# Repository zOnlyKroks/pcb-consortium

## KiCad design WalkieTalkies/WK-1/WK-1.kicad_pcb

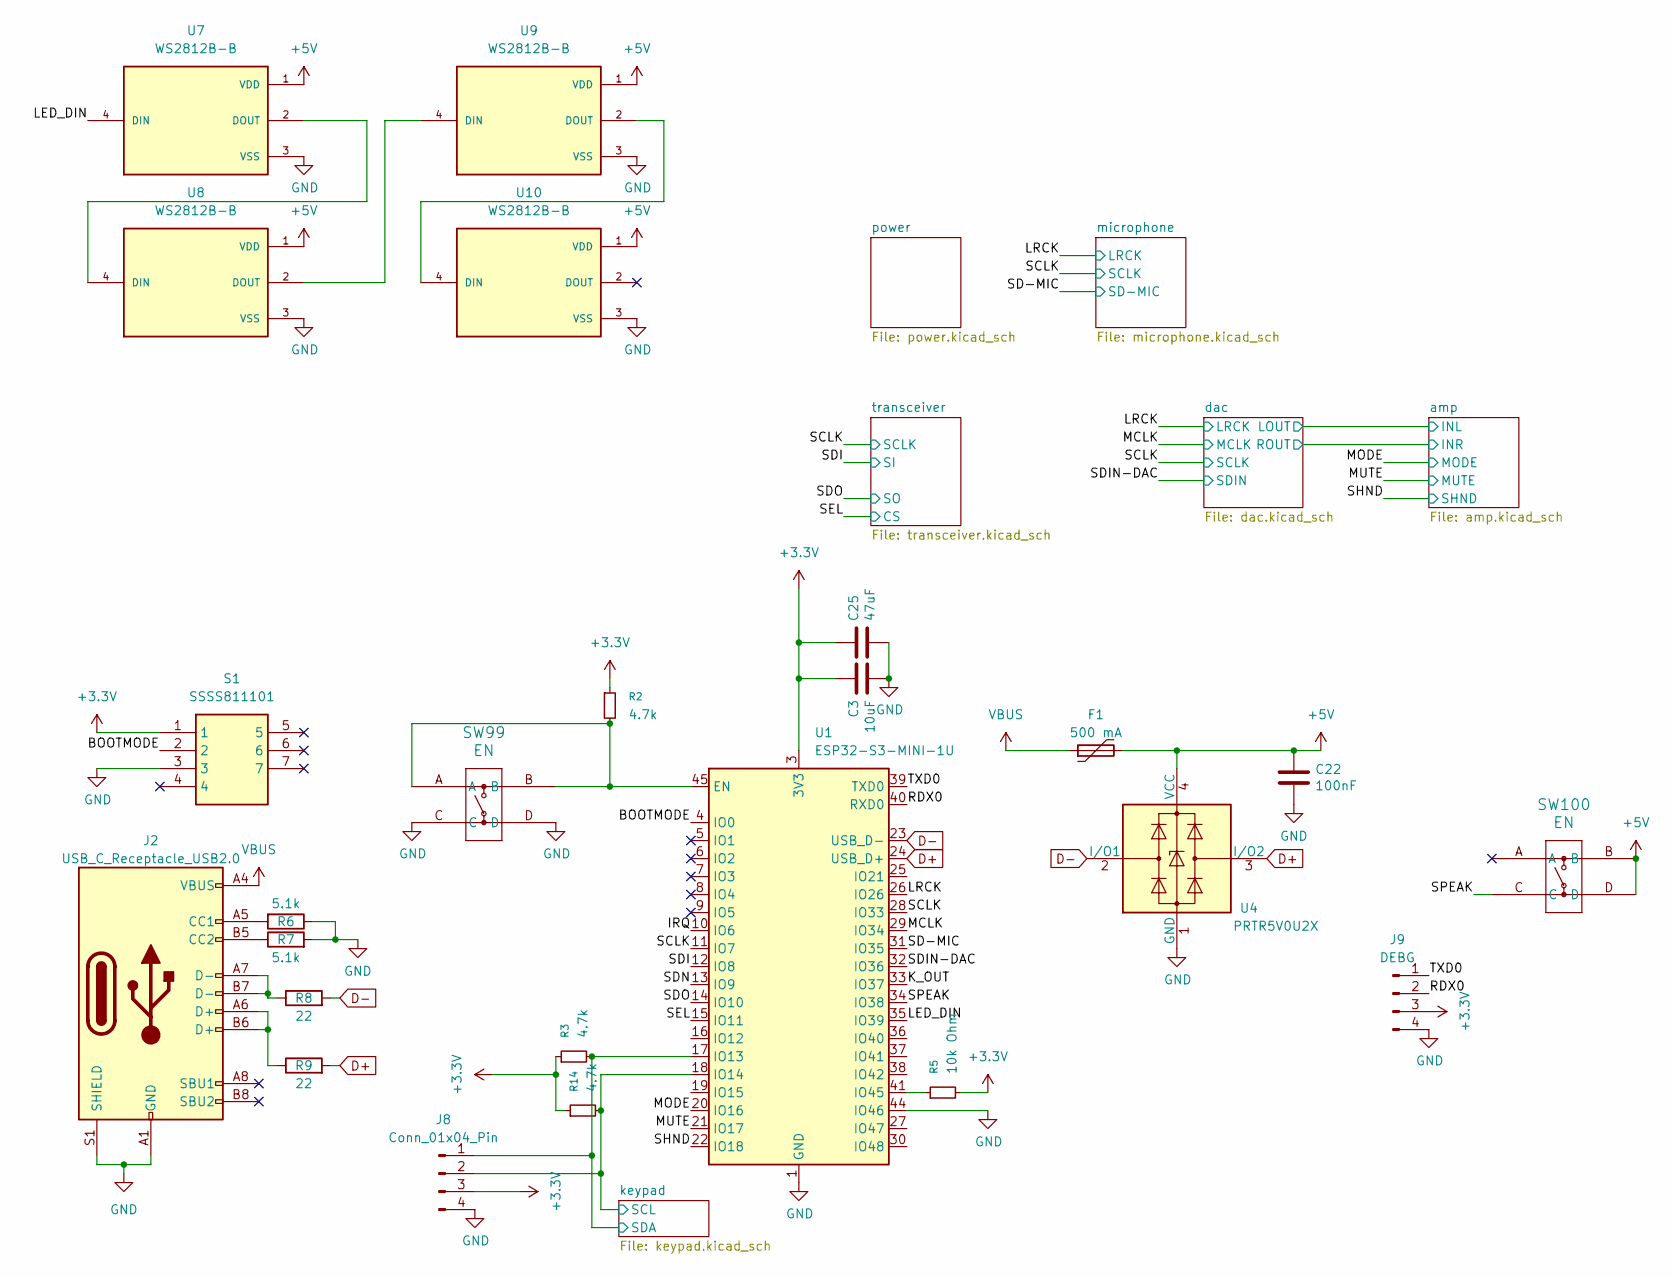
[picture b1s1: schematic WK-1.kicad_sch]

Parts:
C3: 10uF; C_0603_1608Metric; LCSC Part # C19702
C22: 100nF; C_0603_1608Metric; LCSC C14663
C25: 47uF; C_1206_3216Metric; LCSC C96123
F1: 500 mA; Fuse_1206_3216Metric; LCSC Part # C135341
J2: USB_C_Receptacle_USB2.0; USB_C_Receptacle_HRO_TYPE-C-31-M-12; JlcRotOffset 180
J8: Conn_01x04_Pin; PinSocket_1x04_P2.54mm_Vertical; LCSC Part # C5116483
J9: DEBG; PinSocket_1x04_P2.54mm_Vertical; LCSC Part # C5116483
R2, R3, R14: 4.7k; R_0603_1608Metric; LCSC Part # C23162
R5: 10k Ohm; R_0603_1608Metric; LCSC Part # C25804
R6, R7: 5.1k; R_0603_1608Metric; LCSC Part # C23186
R8, R9: 22; R_0603_1608Metric; LCSC Part # C23345
S1: SSSS811101; Mouser Part Number 688-SSSS811101
SW99, SW100: EN; KH-6X6X5H-STM_SKE; LCSC Part # C2837531
U1: ESP32-S3-MINI-1U; ESP32-S2-MINI-1U; LCSC Part # C2980299
U4: PRTR5V0U2X; SOT-143; LCSC Part # C2827688
U7, U8, U9, U10: WS2812B-B; LED_WS2812B-B; PARTREV 5; LCSC Part # C2761795

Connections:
+3.3V: C3.1, C25.1, J8.3, J9.3, R2.1, R3.1, R5.2, R14.1, S1.1, U1.3 (3V3); also elsewhere on the board
+5V: C22.1, F1.2, SW100.B, SW100.D, U4.4 (VCC), U7.1 (VDD), U8.1 (VDD), U9.1 (VDD), U10.1 (VDD); also elsewhere on the board
/BOOTMODE: S1.2, U1.4 (IO0)
/IRQ: U1.10 (IO6)
/K_OUT: U1.33 (IO37)
/LED_DIN: U1.35 (IO39), U7.4 (DIN)
/LRCK: U1.26 (IO26); also elsewhere on the board
/MCLK: U1.29 (IO34); also elsewhere on the board
/MODE: U1.20 (IO16); also elsewhere on the board
/MUTE: U1.21 (IO17); also elsewhere on the board
/RDX0: J9.2, U1.40 (RXD0)
/SCLK: U1.11 (IO7), U1.28 (IO33); also elsewhere on the board
/SD-MIC: U1.31 (IO35); also elsewhere on the board
/SDI: U1.12 (IO8); also elsewhere on the board
/SDIN-DAC: U1.32 (IO36); also elsewhere on the board
/SDN: U1.13 (IO9)
/SDO: U1.14 (IO10); also elsewhere on the board
/SEL: U1.15 (IO11); also elsewhere on the board
/SHND: U1.22 (IO18); also elsewhere on the board
/SPEAK: SW100.C, U1.34 (IO38)
/TXD0: J9.1, U1.39 (TXD0)
/keypad/SCL: J8.2, R14.2, U1.18 (IO14); also elsewhere on the board
/keypad/SDA: J8.1, R3.2, U1.17 (IO13); also elsewhere on the board
D+: R9.2, U1.24 (USB_D+), U4.3 (I/O2)
D-: R8.2, U1.23 (USB_D-), U4.2 (I/O1)
GND: C3.2, C22.2, C25.2, J2.A1 (GND), J2.A12 (GND), J2.B1 (GND), J2.B12 (GND), J2.S1 (SHIELD), J8.4, J9.4, R6.1, R7.2, S1.3, SW99.C, SW99.D, U1.1 (GND), U1.2 (GND), U1.42 (GND), U1.43 (GND), U1.44 (IO46), U1.46 (GND), U1.47 (GND), U1.48 (GND), U1.49 (GND), U1.50 (GND), U1.51 (GND), U1.52 (GND), U1.53 (GND), U1.54 (GND), U1.55 (GND), U1.56 (GND), U1.57 (GND), U1.58 (GND), U1.59 (GND), U1.60 (GND), U1.61 (GND), U1.62 (GND), U1.63 (GND), U1.64 (GND), U1.65 (GND), U4.1 (GND), U7.3 (VSS), U8.3 (VSS), U9.3 (VSS), U10.3 (VSS); also elsewhere on the board
unnamed: J2.A5 (CC1), R6.2
unnamed: J2.B5 (CC2), R7.1
unnamed: J2.A6 (D+), J2.B6 (D+), R9.1
unnamed: J2.A7 (D-), J2.B7 (D-), R8.1
unnamed: R2.2, SW99.A, SW99.B, U1.45 (EN)
unnamed: R5.1, U1.41 (IO45)
unnamed: U7.2 (DOUT), U8.4 (DIN)
unnamed: U8.2 (DOUT), U9.4 (DIN)
unnamed: U9.2 (DOUT), U10.4 (DIN)
VBUS: F1.1, J2.A4 (VBUS), J2.A9 (VBUS), J2.B4 (VBUS), J2.B9 (VBUS)

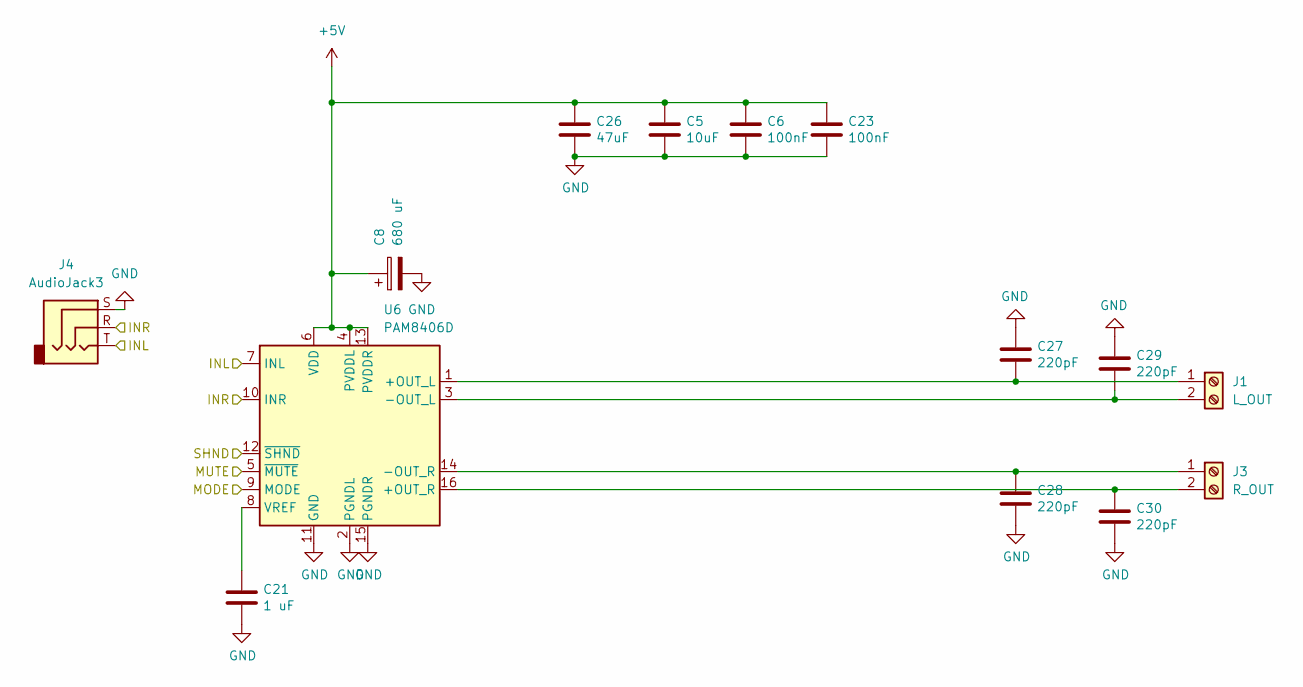
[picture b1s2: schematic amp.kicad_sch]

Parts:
C5: 10uF; C_0603_1608Metric; LCSC Part # C19702
C6, C23: 100nF; C_0603_1608Metric; LCSC Part # C14663
C8: 680 uF; CP_Elec_8x10.5; LCSC Part # C970708
C21: 1 uF; C_0603_1608Metric; LCSC Part # C15849
C26: 47uF; C_1206_3216Metric; LCSC Part # C96123
C27, C28, C29, C30: 220pF; C_0603_1608Metric; LCSC Part # C1603
J1: L_OUT; WJ500V-5.08-2P; LCSC Part # C8465
J3: R_OUT; WJ500V-5.08-2P; LCSC Part # C8465
J4: AudioJack3; Jack_3.5mm_CUI_SJ1-3533NG_Horizontal; LCSC Part # C4992459
U6: PAM8406D; SOIC-16_3.9x9.9mm_P1.27mm; LCSC Part # C86270

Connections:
+5V: C5.1, C6.1, C8.1, C23.1, C26.1, U6.4 (PVDDL), U6.6 (VDD), U6.13 (PVDDR); also elsewhere on the board
/MODE: U6.9 (MODE); also elsewhere on the board
/MUTE: U6.5 (~MUTE); also elsewhere on the board
/SHND: U6.12 (~SHND); also elsewhere on the board
/amp/INL: J4.T, U6.7 (INL); also elsewhere on the board
/amp/INR: J4.R, U6.10 (INR); also elsewhere on the board
GND: C5.2, C6.2, C8.2, C21.2, C23.2, C26.2, C27.1, C28.2, C29.1, C30.2, J4.S, U6.2 (PGNDL), U6.11 (GND), U6.15 (PGNDR); also elsewhere on the board
unnamed: C27.2, J1.1, U6.1 (+OUT_L)
unnamed: C29.2, J1.2, U6.3 (-OUT_L)
unnamed: C28.1, J3.1, U6.14 (-OUT_R)
unnamed: C30.1, J3.2, U6.16 (+OUT_R)
unnamed: C21.1, U6.8 (VREF)

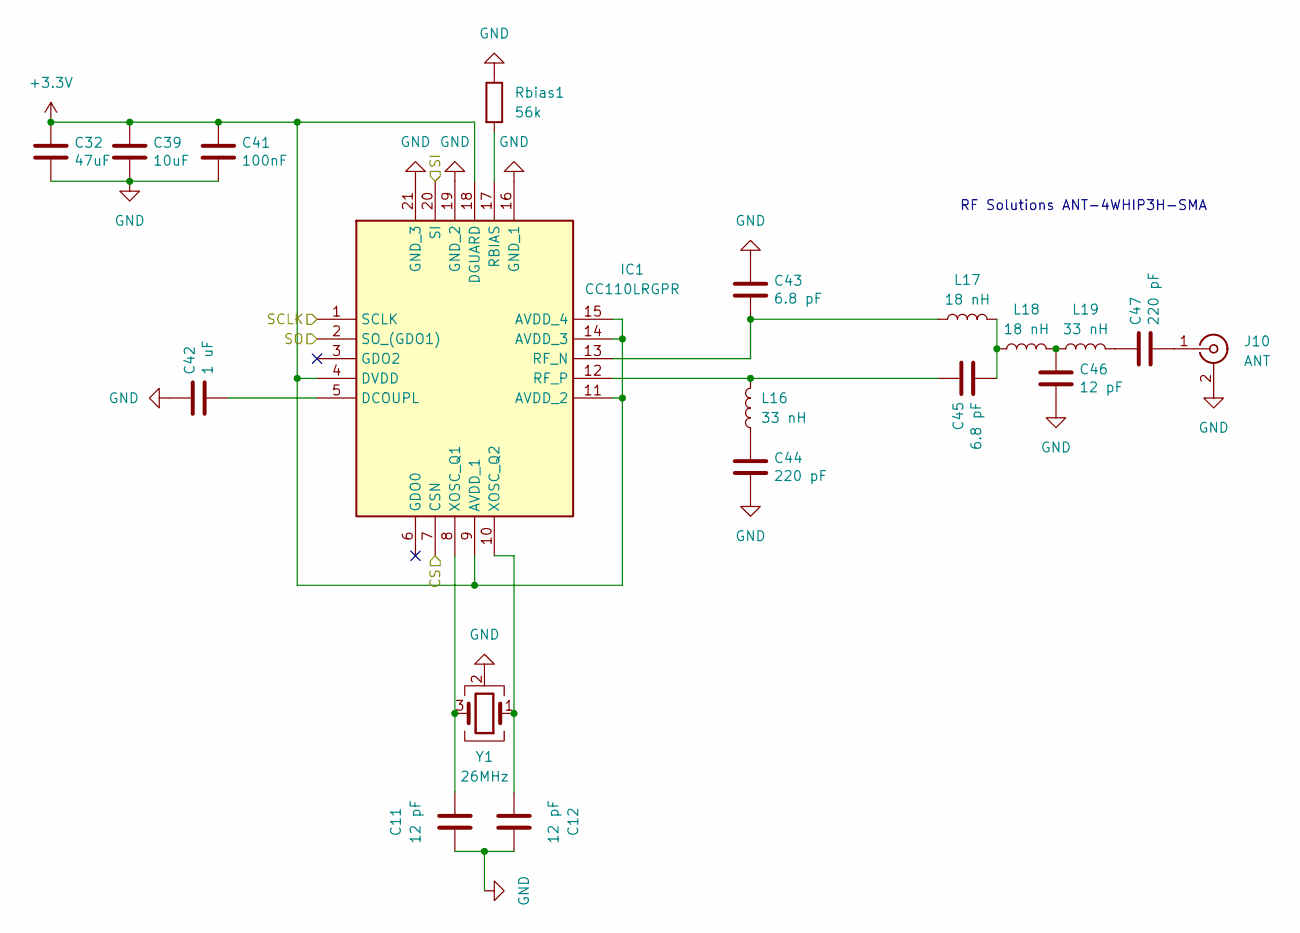
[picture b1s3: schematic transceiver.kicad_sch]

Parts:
C11, C12: 12 pF; C_0603_1608Metric; LCSC Part # C1648
C32: 47uF; C_1206_3216Metric; LCSC Part # C96123
C39: 10uF; C_0603_1608Metric; LCSC Part # C19702
C41: 100nF; C_0603_1608Metric
C42: 1 uF; C_0603_1608Metric; LCSC Part # C19702
C43, C45: 6.8 pF; C_0603_1608Metric
C44, C47: 220 pF; C_0603_1608Metric
C46: 12 pF; C_0603_1608Metric
IC1: CC110LRGPR; QFN50P400X400X100-21N-D; Mouser Part Number 595-CC110LRGPR
J10: ANT; SMA_BAT_Wireless_BWSMA-KWE-Z001; LCSC Part # C496551
L16, L19: 33 nH; L_0805_2012Metric; LCSC Part # C98992
L17, L18: 18 nH; L_0805_2012Metric; LCSC Part # C98992
Rbias1: 56k; R_0603_1608Metric; LCSC Part # C17634
Y1: 26MHz; Crystal_SMD_3225-4Pin_3.2x2.5mm

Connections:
+3.3V: C32.1, C39.1, C41.1, IC1.4 (DVDD), IC1.9 (AVDD_1), IC1.11 (AVDD_2), IC1.14 (AVDD_3), IC1.15 (AVDD_4), IC1.18 (DGUARD); also elsewhere on the board
/SCLK: IC1.1 (SCLK); also elsewhere on the board
/SDI: IC1.20 (SI); also elsewhere on the board
/SDO: IC1.2 (SO_(GDO1)); also elsewhere on the board
/SEL: IC1.7 (CSN); also elsewhere on the board
GND: C11.1, C12.1, C32.2, C39.2, C41.2, C42.1, C43.1, C44.2, C46.2, IC1.16 (GND_1), IC1.19 (GND_2), IC1.21 (GND_3), J10.2 (Ext), Rbias1.1, Y1.2 (G), Y1.4 (G); also elsewhere on the board
unnamed: C44.1, L16.1
unnamed: C45.2, L17.2, L18.1
unnamed: C46.1, L18.2, L19.1
unnamed: C47.1, L19.2
unnamed: C42.2, IC1.5 (DCOUPL)
unnamed: IC1.17 (RBIAS), Rbias1.2
unnamed: C43.2, IC1.13 (RF_N), L17.1
unnamed: C45.1, IC1.12 (RF_P), L16.2
unnamed: C11.2, IC1.8 (XOSC_Q1), Y1.3
unnamed: C12.2, IC1.10 (XOSC_Q2), Y1.1
unnamed: C47.2, J10.1 (In)

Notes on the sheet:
RF Solutions ANT-4WHIP3H-SMA

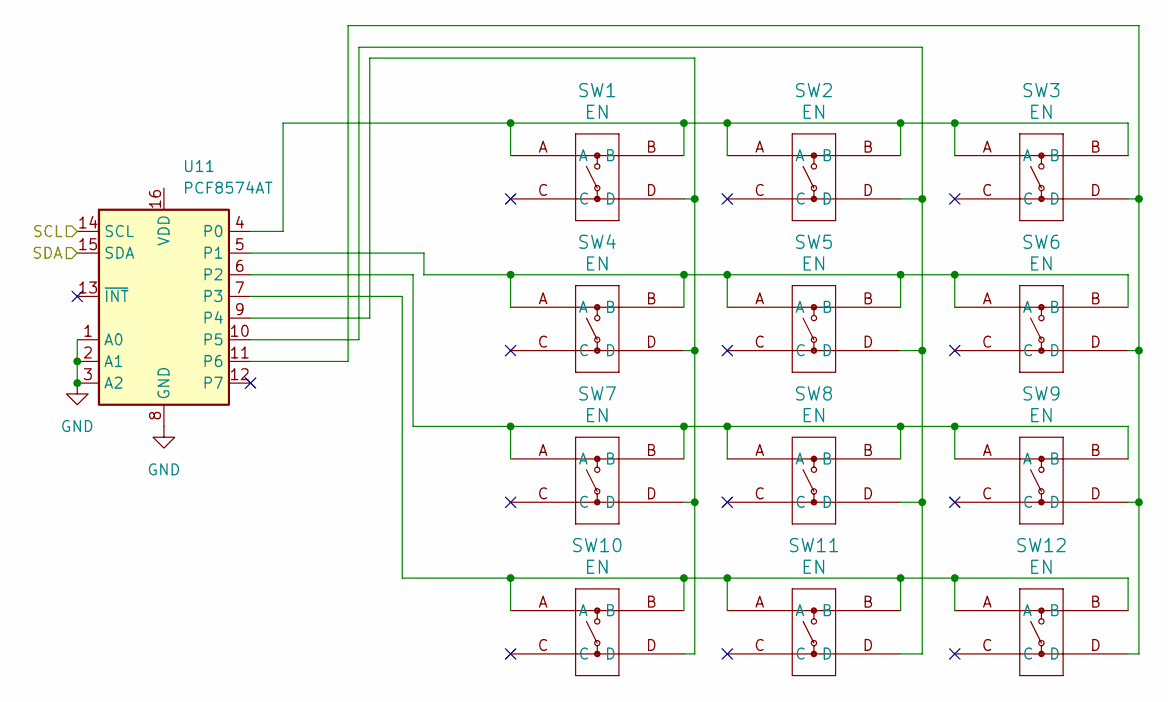
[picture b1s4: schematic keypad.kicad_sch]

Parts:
SW1, SW2, SW3, SW4, SW5, SW6, SW7, SW8, SW9, SW10, SW11, SW12: EN; KH-6X6X5H-STM_SKE; LCSC Part # C2837531
U11: PCF8574AT; SOIC-16W_7.5x10.3mm_P1.27mm; LCSC Part # C2987289

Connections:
/keypad/SCL: U11.14 (SCL); also elsewhere on the board
/keypad/SDA: U11.15 (SDA); also elsewhere on the board
GND: U11.1 (A0), U11.2 (A1), U11.3 (A2), U11.8 (GND); also elsewhere on the board
unnamed: SW1.A, SW1.B, SW2.A, SW2.B, SW3.A, SW3.B, U11.4 (P0)
unnamed: SW4.A, SW4.B, SW5.A, SW5.B, SW6.A, SW6.B, U11.5 (P1)
unnamed: SW7.A, SW7.B, SW8.A, SW8.B, SW9.A, SW9.B, U11.6 (P2)
unnamed: SW10.A, SW10.B, SW11.A, SW11.B, SW12.A, SW12.B, U11.7 (P3)
unnamed: SW1.D, SW4.D, SW7.D, SW10.D, U11.9 (P4)
unnamed: SW2.D, SW5.D, SW8.D, SW11.D, U11.10 (P5)
unnamed: SW3.D, SW6.D, SW9.D, SW12.D, U11.11 (P6)

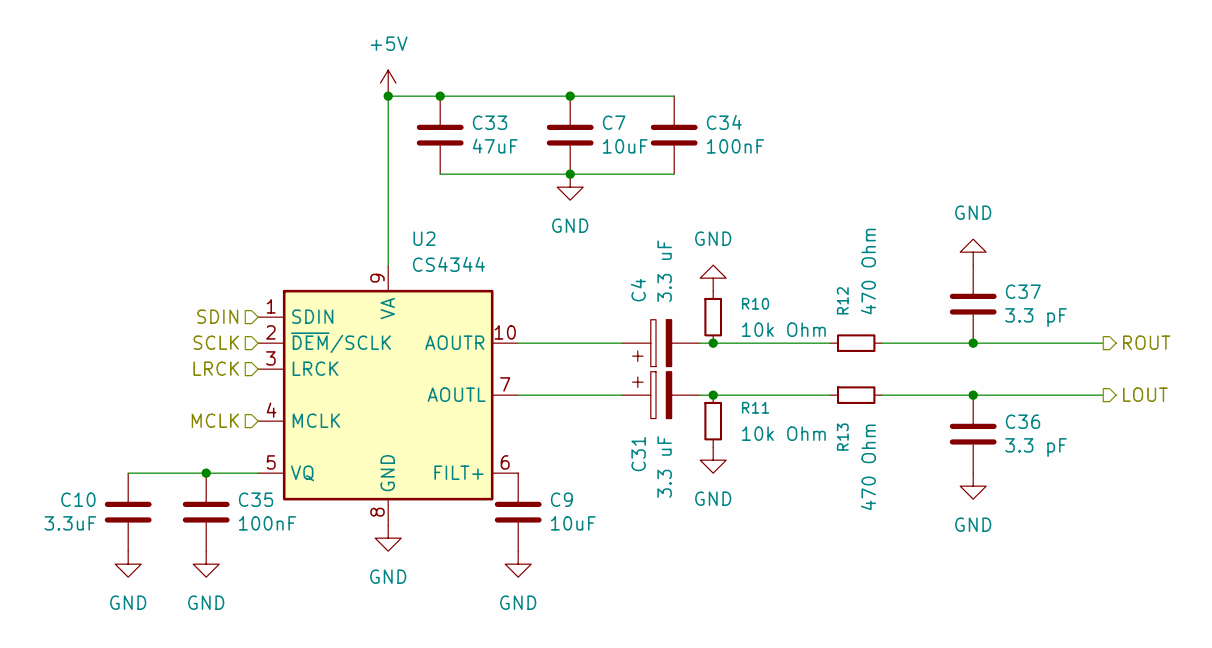
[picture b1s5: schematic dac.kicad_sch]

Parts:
C4, C31: 3.3 uF; CP_Elec_6.3x5.4; LCSC Part # C87855
C7, C9: 10uF; C_0603_1608Metric; LCSC Part # C19702
C10: 3.3uF; C_0603_1608Metric; LCSC Part # C51412
C33: 47uF; C_1206_3216Metric; LCSC Part # C96123
C34: 100nF; C_0603_1608Metric; LCSC Part # C14663
C35: 100nF; C_0603_1608Metric; LCSC C14663
C36, C37: 3.3 pF; C_0603_1608Metric; LCSC Part # C107050
R10, R11: 10k Ohm; R_0603_1608Metric; LCSC Part # C25804
R12, R13: 470 Ohm; R_0603_1608Metric; LCSC Part # C23179
U2: CS4344; TSSOP-10_3x3mm_P0.5mm; LCSC Part # C8952

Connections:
+5V: C7.1, C33.1, C34.1, U2.9 (VA); also elsewhere on the board
/LRCK: U2.3 (LRCK); also elsewhere on the board
/MCLK: U2.4 (MCLK); also elsewhere on the board
/SCLK: U2.2 (~DEM/SCLK); also elsewhere on the board
/SDIN-DAC: U2.1 (SDIN); also elsewhere on the board
/amp/INL: C36.1, R13.2; also elsewhere on the board
/amp/INR: C37.2, R12.2; also elsewhere on the board
GND: C7.2, C9.2, C10.2, C33.2, C34.2, C35.2, C36.2, C37.1, R10.1, R11.2, U2.8 (GND); also elsewhere on the board
unnamed: C4.2, R10.2, R12.1
unnamed: C31.2, R11.1, R13.1
unnamed: C31.1, U2.7 (AOUTL)
unnamed: C4.1, U2.10 (AOUTR)
unnamed: C9.1, U2.6 (FILT+)
unnamed: C10.1, C35.1, U2.5 (VQ)

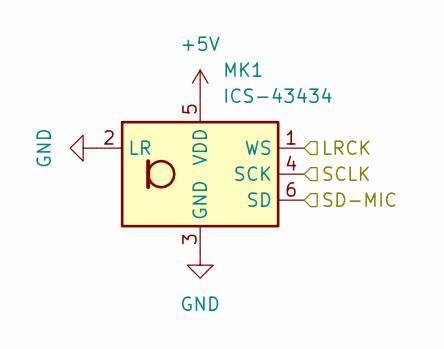
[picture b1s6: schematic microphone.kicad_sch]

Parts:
MK1: ICS-43434; InvenSense_ICS-43434-6_3.5x2.65mm; LCSC Part # C5656610

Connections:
+5V: MK1.5 (VDD); also elsewhere on the board
/LRCK: MK1.1 (WS); also elsewhere on the board
/SCLK: MK1.4 (SCK); also elsewhere on the board
/SD-MIC: MK1.6 (SD); also elsewhere on the board
GND: MK1.2 (LR), MK1.3 (GND); also elsewhere on the board

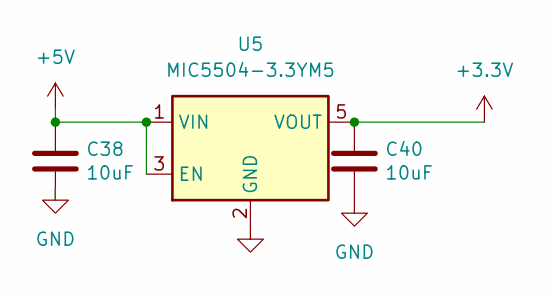
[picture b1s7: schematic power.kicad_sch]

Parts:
C38, C40: 10uF; C_0603_1608Metric; LCSC Part # C19702
U5: MIC5504-3.3YM5; SOT-23-5; LCSC Part # C88419

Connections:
+3.3V: C40.1, U5.5 (VOUT); also elsewhere on the board
+5V: C38.1, U5.1 (VIN), U5.3 (EN); also elsewhere on the board
GND: C38.2, C40.2, U5.2 (GND); also elsewhere on the board

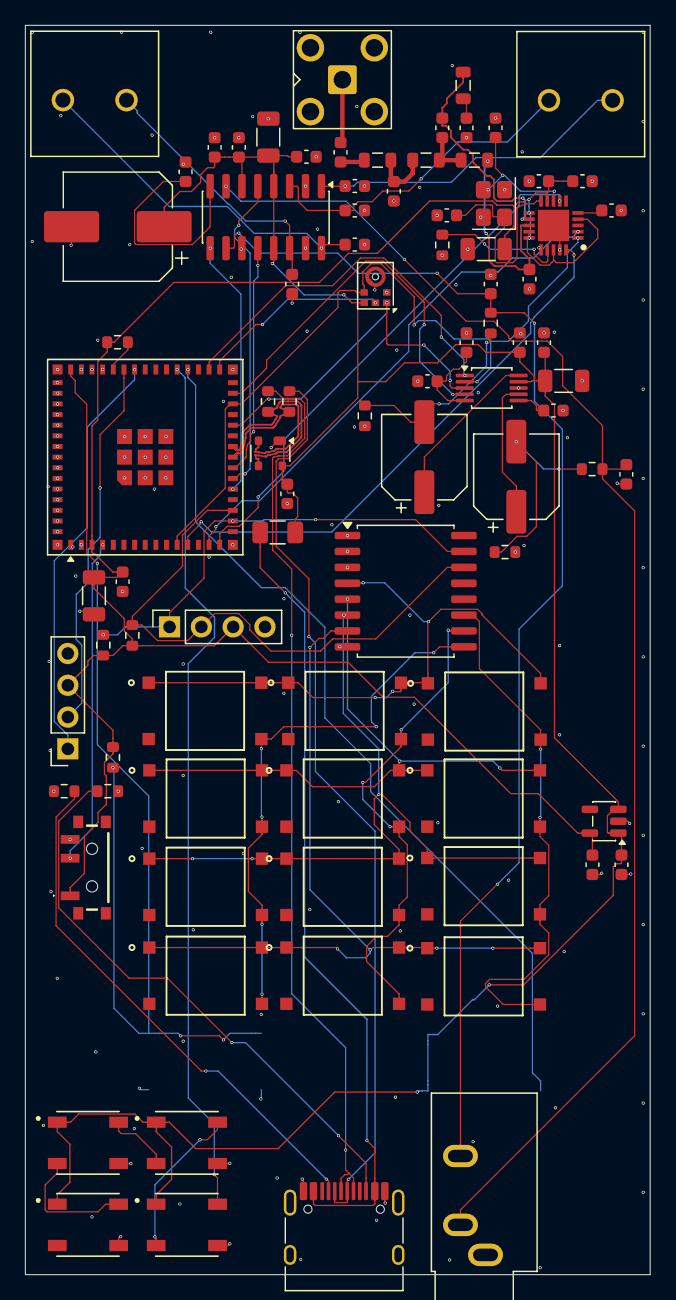
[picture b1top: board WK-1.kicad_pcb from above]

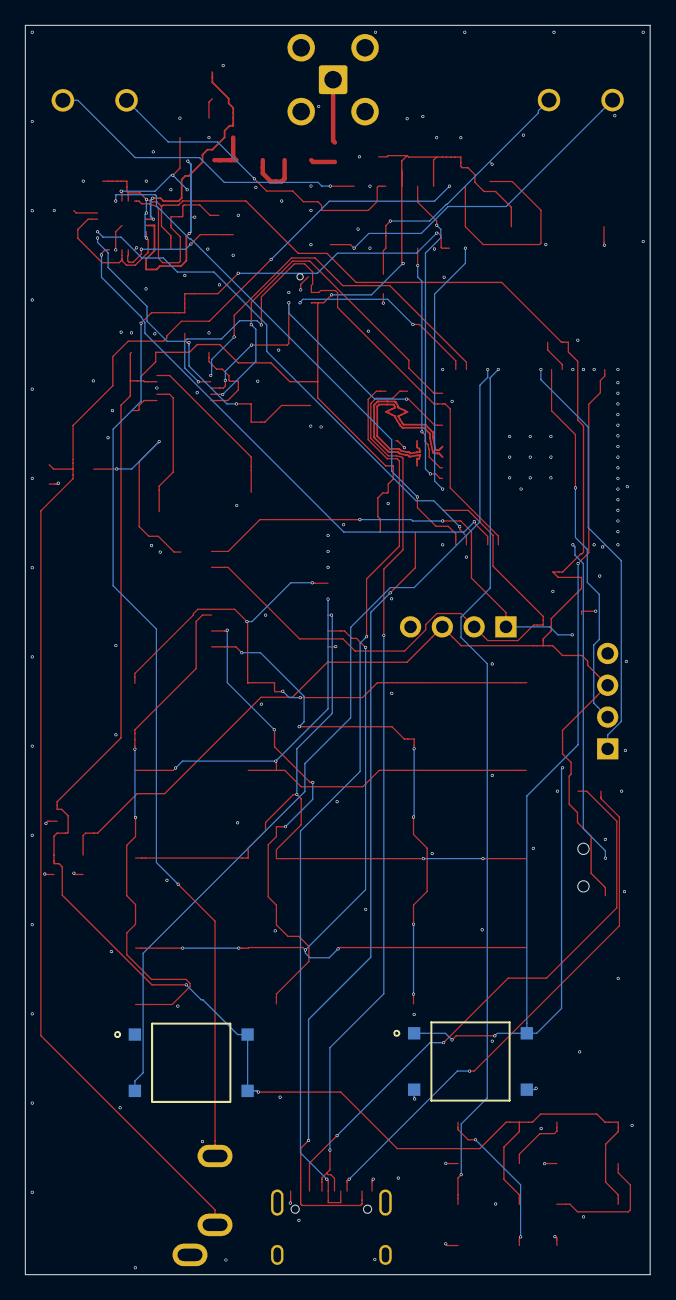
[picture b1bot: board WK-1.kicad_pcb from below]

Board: 4 copper layers, 49.9 x 99.8 mm, 89 parts (2 on the bottom side), 64 nets.

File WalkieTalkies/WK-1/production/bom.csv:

Designator,Footprint,Quantity,Value,LCSC Part #
C10,0603,1,3.3uF,C51412
C11,0603,1,12 pF,C1648 
"C12, C46",0603,2,12 pF,C38523
C21,0603,1,1 uF,C15849
"C22, C23, C34, C35, C41, C6",0603,6,100nF,C14663
"C25, C26, C32, C33",1206,4,47uF,C96123
"C27, C28, C29, C30",0603,4,220pF,C1603
"C3, C38, C39, C40, C5, C7, C9",0603,7,10uF,C19702
"C31, C4",CP_Elec_6.3x5.4,2,3.3 uF,C87855
"C36, C37",0603,2,3.3 pF,C1660
C42,0603,1,1 uF,C19702
"C43, C45",0603,2,6.8 pF,C1679
"C44, C47",0603,2,220 pF,C1603
C8,CP_Elec_8x10.5,1,680 uF,C970708
F1,1206,1,500 mA,C135341
IC1,QFN50P400X400X100-21N-D,1,CC110LRGPR,C56516
J1,WJ500V-5.08-2P,1,L_OUT,C8465
J10,SMA_BAT_Wireless_BWSMA-KWE-Z001,1,ANT,C496551
J2,USB_C_Receptacle_HRO_TYPE-C-31-M-12,1,USB_C_Receptacle_USB2.0,C165948
J3,WJ500V-5.08-2P,1,R_OUT,C8465
J4,Jack_3.5mm_CUI_SJ1-3533NG_Horizontal,1,AudioJack3,C4992459
J8,PinSocket_1x04_P2.54mm_Vertical,1,Conn_01x04_Pin,C5116483
J9,PinSocket_1x04_P2.54mm_Vertical,1,DEBG,C5116483
"L16, L19",0805,2,33 nH,C341796
"L17, L18",0805,2,18 nH,C341795
MK1,InvenSense_ICS-43434-6_3.5x2.65mm,1,ICS-43434,C5656610
"R10, R11, R5",0603,3,10k Ohm,C25804
"R12, R13",0603,2,470 Ohm,C23179
"R14, R2, R3",0603,3,4.7k,C23162
"R6, R7",0603,2,5.1k,C23186
"R8, R9",0603,2,22,C23345
RBIAS1,0603,1,56k,C23206
S1,SSSS811101,1,SSSS811101,C109335
"SW1, SW10, SW100, SW11, SW12, SW2, SW3, SW4, SW5, SW6, SW7, SW8, SW9, SW99",KH-6X6X5H-STM_SKE,14,EN,C2837531 
U1,ESP32-S2-MINI-1U,1,ESP32-S3-MINI-1U,C2980299
"U10, U7, U8, U9",LED_WS2812B-B,4,WS2812B-B,C2761795
U11,SOIC-16W_7.5x10.3mm_P1.27mm,1,PCF8574AT,C2987289
U2,TSSOP-10_3x3mm_P0.5mm,1,CS4344,C8952
U4,SOT-143,1,PRTR5V0U2X,C2827688
U5,SOT-23-5,1,MIC5504-3.3YM5,C88419
U6,SOIC-16_3.9x9.9mm_P1.27mm,1,PAM8406D,C86270
Y2,Crystal_SMD_3225-4Pin_3.2x2.5mm,1,26MHz,C29538

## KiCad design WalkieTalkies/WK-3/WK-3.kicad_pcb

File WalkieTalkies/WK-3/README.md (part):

# WK-3: fully analog 2 m PTT walkie-talkie

A crystal-controlled narrowband-FM transceiver for the 2 m amateur band:
- **No digital parts:** no MCU, no PLL, no DSP and no firmware.
- **No alignment:** there is nothing to tune. Every filter, tank, bias point and level is set by fixed values and has been checked in simulation against component tolerances.
- **Sourcing:** every part comes from LCSC (the `LCSC Part #` field on each symbol), and only stock crystals are used.

> **Licence:** transmitting on 145 MHz needs an amateur radio licence (in Germany Klasse N / E / A). Check your band plan and your licence's power limit. Before going on air, confirm the spurious emissions with a spectrum analyser; simulation is not a substitute.

## Key numbers

| | |
|---|---|
| Channel | **145.400 MHz** simplex (IARU R1 V32), single channel, crystal controlled |
| Mode | NBFM, 12.5 kHz raster, **±2.3 kHz** peak deviation (simulated), 6 dB/oct pre-/de-emphasis |
| TX power | **≥ 1 W on every RFM01U7P of its 0.6–1.6 V threshold spread from a full pack down to mid-charge**: 1.13 W typical, 1.00 W for the highest-threshold part (whole transmitter simulated in one netlist). Driver and PA run from a regulated 7.0 V rail, so the power is the same from 8.4 V down to ≈ 7.1 V. Below that, typical / worst part: 0.99 / 0.89 W at 6.6 V, 0.84 / 0.75 W at the 6.1 V cut-off (datasheet-based model) |
| TX spurs | Harmonics −80 / −123 dBc. Strongest other emission anywhere from 30 MHz to 1 GHz: −86 dBc (≈ −55.5 dBm, 2LO − 2IF at 141.2 MHz), 19 dB under the −36 dBm CEPT limit. The PA is stable with no drive at every tolerance corner, and its drain stays under its 20 V rating (19.0 V worst case) |
| RX | LNA + J310 mixer → 37.4 MHz 4-crystal ladder (≈14 kHz) → MC3361 (1 MHz 2nd IF) → LM386. Image rejection 52 dB, LO rejection 52 dB |
| Supply | **2 × 18650 in series**, in two MYOUNG BH-18650-B1BA002 SMD holders on the back of the board (6.0–8.4 V). Under-voltage cut-off: off below ≈ 6.06 V (5.91–6.22 V worst case), back on only above ≈ 6.58 V (6.41–6.76 V). The 0.5 V hysteresis keeps the switch-over clean even with worn or cold cells. Nothing draws current when switched off. Charge the cells outside the radio. A TL1963A makes the 7.0 V PA / driver rail. Do **not** exceed 9 V (AO3401A V<sub>GS</sub>, 2SC3357 V<sub>CEO</sub>) |
| Current | TX ≈ 385 mA from the battery (driver + PA, simulated; ≤ 419 mA on a low-threshold PA) plus about 60 mA on the 5 V rail and 3 mA for the cut-off. RX ≈ 57–67 mA (estimate, including 1.5 mA for the PA regulator) |

**Range:** at 1 W (+30 dBm) with −5 dBi handhelds 1.5 m above open ground, the plane-earth loss at 2 km is about 125 dB. That leaves roughly 14 dB of margin over a −119 dBm receiver: about 2.5 km with a solid link and 4.5 km at the edge on open ground, 1–2 km in town, and 10–40 km from high ground with line of sight.

## Frequency plan (stock crystals only)

```
LO:  Y501 54.000 MHz (10 pF) VXO, FM via 1SV305 on MOD  -> x2 (damped tanks) -> 108.000 MHz
     -> fixed 3-pole 108 MHz band-pass -> LO_TX (TX mixer) / LO_RX (RX mixer)

TX:  mic -> LMV324 pre-emphasis / limiter / 3 kHz splatter filter -> fixed divider -> MOD (FM on the 54 MHz VXO)
     Y201 37.400 MHz osc -> 50 MHz LPF -> ETC1-1-13 -> MC1496 Gilbert mixer (LO 108 via ETC1-1-13) -> ETC1-1-13
     -> elliptic HPF #1 -> 7-pole elliptic LPF -> 2SC3356 -> elliptic HPF #2 -> 2SC3356 (+4 dBm)
     -> 2SC3357 driver -> RFM01U7P (7.0 V rail, fixed 2.5 V gate bias, drain-gate RC feedback) -> pi-match -> PIN T/R -> 7-pole LPF -> SMA
     108.0 + 37.4 = 145.4 MHz

RX:  SMA -> 7-pole LPF -> PIN T/R -> elliptic HPF (zeros 108 / 94 / 59 MHz) -> 2SC3356 LNA
     -> J310 mixer (LO 108 on the source) -> 37.4 MHz -> 4 x 37.400 MHz ladder -> 2SC3356 IF amp
     -> MC3361 (Y601 38.400 MHz) -> 1.0 MHz LC IF -> limiter -> quad detector -> de-emphasis
     -> volume -> LM386 -> 8 ohm;  10 kHz noise squelch
```

The same 108 MHz LO serves both directions, so a constant LO error moves TX and RX together. Between two WK-3 radios, only the crystal tolerances (±10 ppm) remain.

## Why nothing needs trimming

- **No resonant filters that need tuning.** The RX and TX band-limiting uses *fixed* 7th-order elliptic high-pass filters and Chebyshev low-pass filters with wide passbands (`tools/design_hpf.py`). They are verified by Monte Carlo over C ±2 % / L ±5 %.
- **Crystals at their rated load.** The VXO presents 10.9 pF to the 10 pF crystal (−13 ppm), and the TX offset oscillator presents ≈9 pF to the 9 pF crystal. FM is applied to the VXO with a fixed bias, so no netting trimmer is needed. Start-up margin is >4× on a 40 Ω max-ESR crystal, with ≈90 µW crystal drive.
- **Damped LO tanks plus a fixed band-pass.** The ×2 tanks are deliberately low-Q, so the inductor tolerance can't detune them. A wide (25 %) fixed 3-pole band-pass then cleans the LO to ≤ −50 dBc (`tools/design_lobpf.py`).
- **IF filter terminations chosen by simulation.** The ladder's terminations were picked over the crystal spread of a whole reel (`tools/design_ladder.py`). The IF amplifier's gain is held to ≈ 13 dB (R609 100 Ω, R608 680 Ω), so its Miller capacitance doesn't detune the last crystal: ripple 1.0 dB with typical crystals.
- **Fixed TX levels.** The MC1496's IF and LO levels and the gain resistor are set by fixed resistors. The PA runs from a fixed 2.5 V gate bias on a regulated 7.0 V rail, so there is no I<sub>dq</sub> to adjust. Every PA check passes across the RFM01U7P's full 0.6–1.6 V threshold spread, including ≥ 1 W and a drain peak under its 20 V rating. A 680 Ω + 100 pF drain-to-gate network keeps the stage stable with no drive. Deviation is set by a fixed divider after the limiter.
- **Low-Q IF2 networks.** The MC3361's 1 MHz IF filter and quadrature tank are wide enough that 5 % parts stay inside their usable range.

## Sheets

| Sheet | Contents |
|---|---|
| `power` | 2 × 18650 holders (BT101 / BT102, on the back), 0.75 A polyfuse, AO3401A reverse-polarity FET, AO3401A power FET (Q105) turned on by the slide switch through a TL431 under-voltage cut-off (U102, R106–R109, C108), LP2985-5.0. PTT switching: Q102 drives `TX5`, Q103/Q104 drive `RX5`. Power and TX LEDs. |
| `tx_exciter` | Electret mic. LMV324 pre-emphasis preamp, limiter, 3 kHz splatter filter and VREF buffer. Deviation divider → `MOD`. 37.4 MHz oscillator, 50 MHz LPF. MC1496 mixer with three ETC1-1-13 baluns: IF in, LO in (balanced, T203) and output. Elliptic HPF #1 → `TXH1_OUT`. |
| `tx_amp` | 7-pole elliptic LPF (removes the mixer's 2LO−IF, 2LO and 3LO±IF before any amplifier), 2SC3356, elliptic HPF #2, 2SC3356 → `TX_RF`. |
| `tx_pa` | TL1963A 7.0 V rail for driver and PA (U301, R311 / R312, C315 / C316). 2SC3357 class-A driver, interstage match, Toshiba RFM01U7P with fixed 2.5 V gate bias and drain-gate RC feedback (R310 / C313), pi-match (C314, L304, C312) → `PA_OUT`. |
| `rf_frontend` | SMA, 7-pole LPF, BAR64 PIN T/R switch with lumped λ/4, elliptic HPF, 2SC3356 LNA → `RX_RF`. |
| `lo` | 54 MHz VXO, ×2 tank, buffer, emitter follower, 3-pole 108 MHz band-pass → `LO_TX` / `LO_RX`. |
| `rx_if` | J310 mixer, 37.4 MHz ladder, 2SC3356 IF amp, MC3361, de-emphasis, volume, noise squelch. |
| `audio` | LM386 (gain ≈40) → 8 Ω speaker. |

Every sheet is drawn with real wires and junctions. GND and the supply rails use power symbols. Neighbouring pins on the same rail share one symbol via a short bus wire. Labels appear only where a signal crosses sheets. Text placement is collision-checked on every build (`tools/cosmetic_check.py`).

## Simulation (KiCad's built-in simulator)

`sim/` holds ten stand-alone KiCad projects. Each contains a section of the real circuit (same references, values and wiring) plus test-bench parts numbered 9xx: sources, 50 Ω ports and supplies. Every part carries `Sim.*` fields pointing at `sim/wk3_models.lib`.

To use one:
1. Open `sim/<bench>/<bench>.kicad_pro`.
2. In the schematic editor, choose **Inspect → Simulator** and press **Run**.
3. Plots are pre-configured. The two-tab benches (`tx_mixer`, `tx_pa`, `lo_chain`) have a TRAN tab and an FFT tab: run TRAN first, then FFT.

| Bench | Analysis | Shows |
|---|---|---|
| `rx_frontend` | AC | Gain into the J310 gate, antenna match, image / LO / FM-broadcast rejection |
| `tx_rf_chain` | AC | HPF + LPF + amplifier transfer: LO, LO−IF, IF and 3LO±IF rejection |
| `tx_mixer` | TRAN + FFT | MC1496 up-conversion and the TX_RF spectrum (spurs) |
| `tx_pa` | TRAN + FFT | Output power, harmonics, battery current, efficiency, idle stability (drive off, kicked, at nominal and worst-case FET), drain peak on a full pack |
| `lo_chain` | TRAN + FFT | VXO start-up, LO level and purity. Runs ≈1 min: the real crystal needs ~0.5 ms to settle |
| `if_ladder` | AC | 37.4 MHz ladder passband / skirts (change `Cm` on the crystals to see the spread) |
| `if2_quad` | AC | MC3361 1 MHz IF filter and quadrature tank |
| `mic_chain` | AC + TRAN | Pre-emphasis, splatter roll-off, limiting |
| `squelch_audio` | AC | De-emphasis / volume and the 10 kHz noise-squelch filter |
| `power` | TRAN | Battery switch and TL431 cut-off while transmitting: switching points, Q105's drop, a worn pack (1.5 Ω) held at every voltage near the threshold and recovering (no half-on state, no chatter), current when switched off |

`python tools/sim_benches.py` rebuilds every bench, then exports each one with `kicad-cli` and runs it in KiCad's own ngspice. It writes **`sim/RESULTS.md`**; currently **84 / 84 checks pass**. Two of the groups are cross-bench:
- **Deviation:** the limiter's clip level through the VXO's pull curve gives ±2.3 kHz peak.
- **Whole transmitter (`tx_chain`):** the `tx_mixer` and `tx_pa` benches are joined into one netlist, so the real exciter output (every mixer product, amp 2's harmonics) drives the real PA. Spurs are read at the antenna, both for a list of known products and as the strongest line anywhere from 30 MHz to 1 GHz. It also checks ≥ 1 W with the highest-threshold PA, the battery current with the lowest-threshold one, and the PA drain peak on a full pack at every threshold. This check found the problems described below; each bench on its own had passed.

**Pictures:** `python tools/sim_plots.py` draws `sim/plots/`: an overview of the radio, one picture per bench (plots, a plain-language explanation and the check table), the whole transmitter (11), PA stability with no drive (12) and the battery cut-off (13).

**TX spurious fix (2026-10-11).** The first design drove the MC1496's LO port on one pin. The LO common-mode swing on the switching quad made 2LO − IF (178.6 MHz) at −29 dBc. That is just above the 164 MHz antenna low-pass corner, so it left the antenna at −43 dBc (≈ −13 dBm, in DAB band III). Fixes:
- a third ETC1-1-13 (T203) now drives pins 8 / 10 in antiphase;
- C262 is gone and R246 is 2.2k;
- two capacitors (C259 10 pF across L248, C265 8.2 pF across L249) make the TX low-pass elliptic, adding at least 14 dB at 178.6 MHz in a ±5 % Monte Carlo;
- R219 = 100 Ω lowers the IF drive, which lowers 2LO − 2IF and 4·IF.

Now 178.6 MHz is −79 dBc at TX_RF.

**Close-in products, PA stability, 1 W (2026-10-11).**
- **Mixer products 4–9 MHz either side of the carrier (−85 dBc):** the MC1496 now runs more linearly (R250 = 220 Ω emitter degeneration), with amp 1's gain raised (R222 = 2.2k) to make up the level.
- **PA oscillation:** the PA oscillated near 220 MHz whenever it was biased without drive, which happens on every PTT press before the 37.4 MHz oscillator starts. R310 (680 Ω) + C313 (100 pF) from drain to gate fix it at all 72 threshold / feedback-capacitance / gain / L302 / L304 tolerance corners tested.
- **1 W on every part:** gate bias 2.0 V (R307 1k, R309 680) and a re-fitted interstage (C304 47p, C305 15p, L302 33n).
- **Trade-off:** the PA now runs less saturated, so the 141.2 MHz product stays at −88.7 dBc instead of the −96 dBc a saturated PA gave; still 22 dB under the limit.
- **Simulation accuracy:** benches that look for products near −90 dBc must use a ≤ 10 ps time step. At 50 ps the close-in products were overstated by 12–30 dB and aliases appeared as fake lines.

**Battery cut-off hysteresis (2026-10-12).** The cut-off had only 0.28 V of hysteresis (R107 15k, R109 330k).
- **The problem:** when the pack's series resistance is 1 Ω or more (worn or cold cells, the holder contacts, a polyfuse that has tripped once), the radio could hang near the threshold while transmitting.
  - The current drop as Q105 opens raises the pack voltage by more than the hysteresis, so the cut-off can't snap off.
  - The `power` bench showed Q105 settling half-on at up to 0.56 W, and switching 71 times while the pack recovered.
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
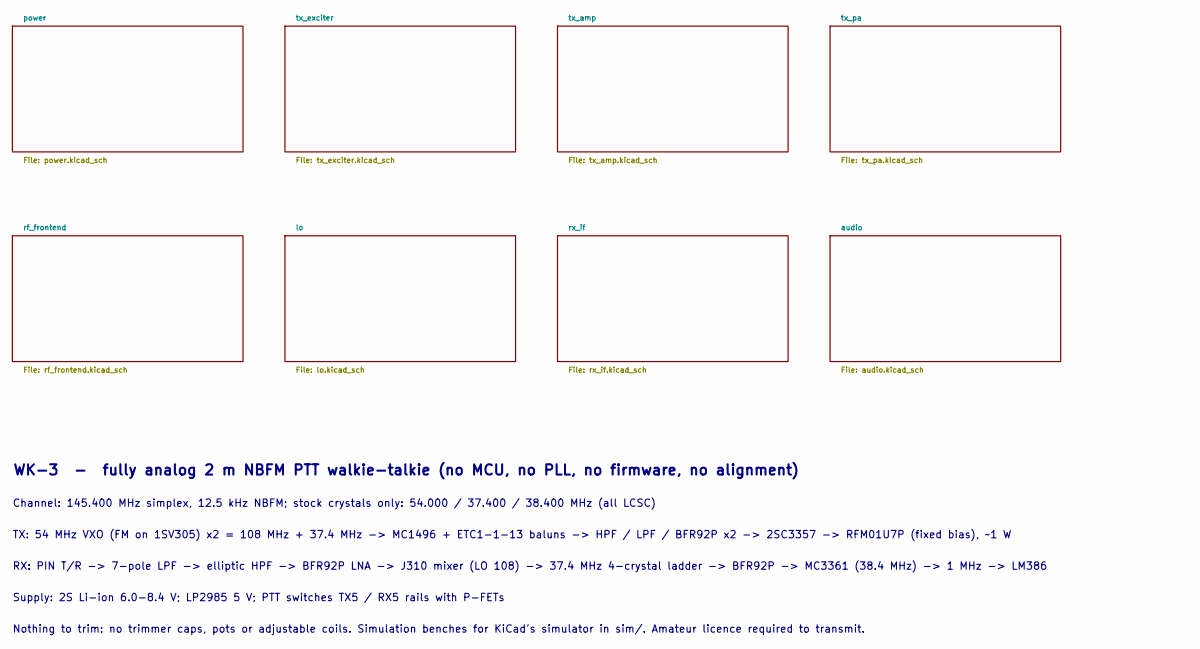
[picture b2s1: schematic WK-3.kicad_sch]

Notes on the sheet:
RX: PIN T/R -> 7-pole LPF -> elliptic HPF -> BFR92P LNA -> J310 mixer (LO 108) -> 37.4 MHz 4-crystal ladder -> BFR92P -> MC3361 (38.4 MHz) -> 1 MHz -> LM386
WK-3 - fully analog 2 m NBFM PTT walkie-talkie (no MCU, no PLL, no firmware, no alignment)
Nothing to trim: no trimmer caps, pots or adjustable coils. Simulation benches for KiCad's simulator in sim/. Amateur licence required to transmit.
Channel: 145.400 MHz simplex, 12.5 kHz NBFM; stock crystals only: 54.000 / 37.400 / 38.400 MHz (all LCSC)
Supply: 2S Li-ion 6.0-8.4 V; LP2985 5 V; PTT switches TX5 / RX5 rails with P-FETs
TX: 54 MHz VXO (FM on 1SV305) x2 = 108 MHz + 37.4 MHz -> MC1496 + ETC1-1-13 baluns -> HPF / LPF / BFR92P x2 -> 2SC3357 -> RFM01U7P (fixed bias), ~1 W

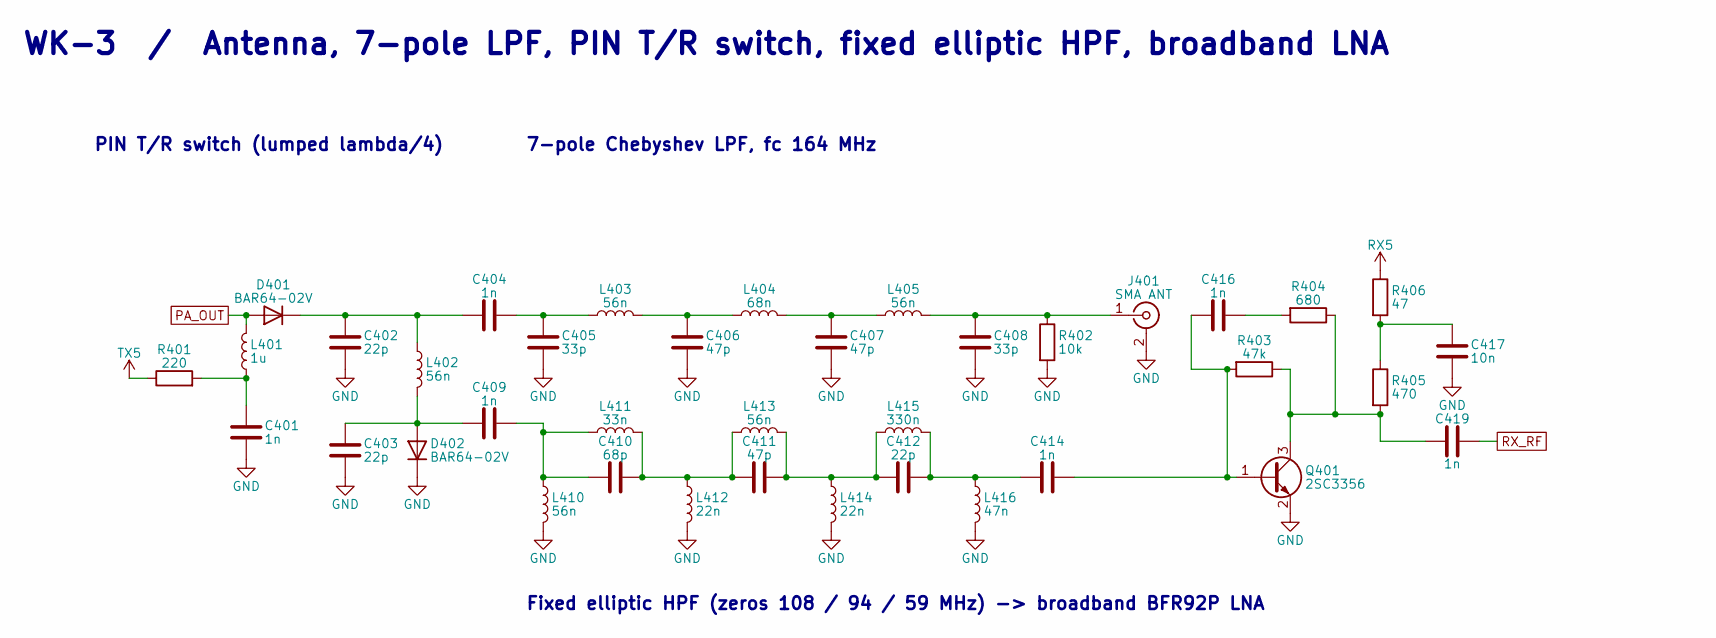
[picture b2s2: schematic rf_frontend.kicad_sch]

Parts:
C401, C404, C409, C414, C416, C419: 1n; C_0603_1608Metric; LCSC Part # C1588
C402, C403, C412: 22p; C_0603_1608Metric; LCSC Part # C1653
C405, C408: 33p; C_0603_1608Metric; LCSC Part # C1663
C406, C407, C411: 47p; C_0603_1608Metric; LCSC Part # C1671
C410: 68p; C_0603_1608Metric; LCSC Part # C62782
C417: 10n; C_0603_1608Metric; LCSC Part # C57112
D401, D402: BAR64-02V; D_SOD-523; LCSC Part # C5295579
J401: SMA ANT; SMA_BAT_Wireless_BWSMA-KWE-Z001; LCSC Part # C496551
L401: 1u; L_0805_2012Metric; LCSC Part # C6808030
L402, L403, L405, L410, L413: 56n; L_0805_2012Metric; LCSC Part # C6808040
L404: 68n; L_0805_2012Metric; LCSC Part # C6808042
L411: 33n; L_0805_2012Metric; LCSC Part # C6808037
L412, L414: 22n; L_0805_2012Metric; LCSC Part # C6808033
L415: 330n; L_0805_2012Metric; LCSC Part # C6364716
L416: 47n; L_0805_2012Metric; LCSC Part # C6808039
Q401: 2SC3356; SOT-23; LCSC Part # C193010
R401: 220; R_0603_1608Metric; LCSC Part # C22962
R402: 10k; R_0603_1608Metric; LCSC Part # C2906982
R403: 47k; R_0603_1608Metric; LCSC Part # C2907042
R404: 680; R_0603_1608Metric; LCSC Part # C23228
R405: 470; R_0603_1608Metric; LCSC Part # C23179
R406: 47; R_0603_1608Metric; LCSC Part # C23182

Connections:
GND: C401.2, C402.2, C403.2, C405.2, C406.2, C407.2, C408.2, C417.2, D402.1 (K), J401.2 (Ext), L410.2, L412.2, L414.2, L416.2, Q401.2 (E), R402.2; also elsewhere on the board
unnamed: C401.1, L401.1, R401.2
unnamed: C404.2, C405.1, L403.1
unnamed: C406.1, L403.2, L404.1
unnamed: C407.1, L404.2, L405.1
unnamed: C409.2, C410.1, L410.1, L411.1
unnamed: C410.2, C411.1, L411.2, L412.1, L413.1
unnamed: C411.2, C412.1, L413.2, L414.1, L415.1
unnamed: C412.2, C414.1, L415.2, L416.1
unnamed: C416.1, R404.2
unnamed: C417.1, R405.1, R406.2
unnamed: C402.1, C404.1, D401.1 (K), L402.1
unnamed: C403.1, C409.1, D402.2 (A), L402.2
unnamed: C408.1, J401.1 (In), L405.2, R402.1
unnamed: C414.2, C416.2, Q401.1 (B), R403.2
unnamed: C419.1, Q401.3 (C), R403.1, R404.1, R405.2
PA_OUT: D401.2 (A), L401.2; also elsewhere on the board
RX5: R406.1; also elsewhere on the board
RX_RF: C419.2; also elsewhere on the board
TX5: R401.1; also elsewhere on the board

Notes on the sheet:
WK-3 / Antenna, 7-pole LPF, PIN T/R switch, fixed elliptic HPF, broadband LNA
PIN T/R switch (lumped lambda/4)
7-pole Chebyshev LPF, fc 164 MHz
Fixed elliptic HPF (zeros 108 / 94 / 59 MHz) -> broadband BFR92P LNA

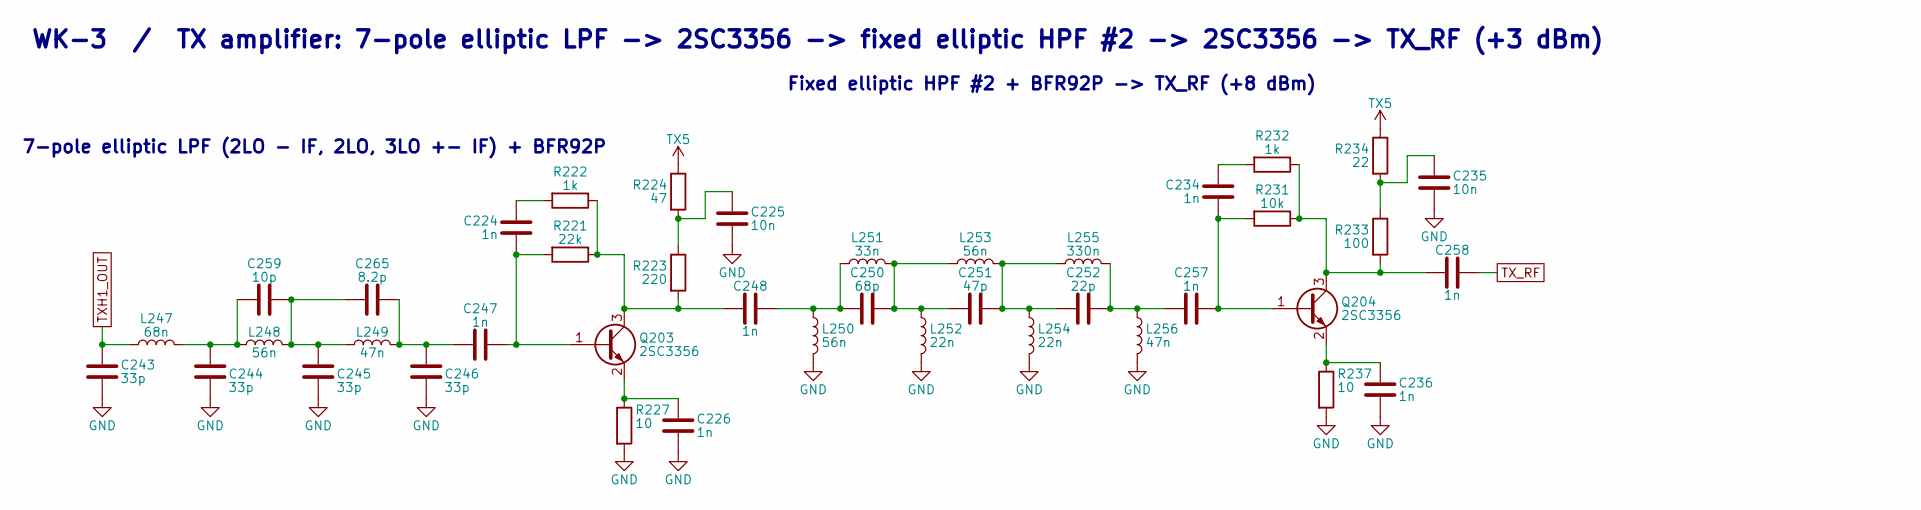
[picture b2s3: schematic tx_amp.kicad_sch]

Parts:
C224, C226, C234, C236, C247, C248, C257, C258: 1n; C_0603_1608Metric; LCSC Part # C1588
C225, C235: 10n; C_0603_1608Metric; LCSC Part # C57112
C243, C244, C245, C246: 33p; C_0603_1608Metric; LCSC Part # C1663
C250: 68p; C_0603_1608Metric; LCSC Part # C62782
C251: 47p; C_0603_1608Metric; LCSC Part # C1671
C252: 22p; C_0603_1608Metric; LCSC Part # C1653
C259: 10p; C_0603_1608Metric; LCSC Part # C1634
C265: 8.2p; C_0603_1608Metric; LCSC Part # C1685
L247: 68n; L_0805_2012Metric; LCSC Part # C6808042
L248, L250, L253: 56n; L_0805_2012Metric; LCSC Part # C6808040
L249, L256: 47n; L_0805_2012Metric; LCSC Part # C6808039
L251: 33n; L_0805_2012Metric; LCSC Part # C6808037
L252, L254: 22n; L_0805_2012Metric; LCSC Part # C6808033
L255: 330n; L_0805_2012Metric; LCSC Part # C6364716
Q203, Q204: 2SC3356; SOT-23; LCSC Part # C193010
R221: 22k; R_0603_1608Metric; LCSC Part # C31850
R222, R232: 1k; R_0603_1608Metric; LCSC Part # C21190
R223: 220; R_0603_1608Metric; LCSC Part # C22962
R224: 47; R_0603_1608Metric; LCSC Part # C23182
R227, R237: 10; R_0603_1608Metric; LCSC Part # C22859
R231: 10k; R_0603_1608Metric; LCSC Part # C2906982
R233: 100; R_0603_1608Metric; LCSC Part # C22775
R234: 22; R_0603_1608Metric; LCSC Part # C23345

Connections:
GND: C225.2, C226.2, C235.2, C236.2, C243.2, C244.2, C245.2, C246.2, L250.2, L252.2, L254.2, L256.2, R227.2, R237.2; also elsewhere on the board
unnamed: C224.1, R222.2
unnamed: C225.1, R223.1, R224.2
unnamed: C234.1, R232.2
unnamed: C235.1, R233.1, R234.2
unnamed: C244.1, C259.1, L247.2, L248.1
unnamed: C245.1, C259.2, C265.1, L248.2, L249.1
unnamed: C246.1, C247.1, C265.2, L249.2
unnamed: C248.2, C250.1, L250.1, L251.1
unnamed: C250.2, C251.1, L251.2, L252.1, L253.1
unnamed: C251.2, C252.1, L253.2, L254.1, L255.1
unnamed: C252.2, C257.1, L255.2, L256.1
unnamed: C224.2, C247.2, Q203.1 (B), R221.2
unnamed: C248.1, Q203.3 (C), R221.1, R222.1, R223.2
unnamed: C226.1, Q203.2 (E), R227.1
unnamed: C234.2, C257.2, Q204.1 (B), R231.2
unnamed: C258.1, Q204.3 (C), R231.1, R232.1, R233.2
unnamed: C236.1, Q204.2 (E), R237.1
TX5: R224.1, R234.1; also elsewhere on the board
TXH1_OUT: C243.1, L247.1; also elsewhere on the board
TX_RF: C258.2; also elsewhere on the board

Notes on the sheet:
WK-3 / TX amplifier: 7-pole elliptic LPF -> 2SC3356 -> fixed elliptic HPF #2 -> 2SC3356 -> TX_RF (+3 dBm)
7-pole elliptic LPF (2LO - IF, 2LO, 3LO +- IF) + BFR92P
Fixed elliptic HPF #2 + BFR92P -> TX_RF (+8 dBm)
